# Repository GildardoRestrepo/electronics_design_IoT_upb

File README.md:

# Diseño Electrónico — UPB

Este repositorio reúne todas las actividades del curso **Diseño Electrónico** (UPB). El curso combina una parte **teórica sobre inteligencia artificial** y una parte **práctica sobre IoT, sistemas embebidos y diseño electrónico**: firmware para ESP32, servidores MQTT, dashboards y diseño de PCB en KiCad.

**Autor:** Gildardo Estevan Restrepo Duque

## Actividades

| #  | Actividad                                   | Carpeta                                                | Bitácora                                                                 |
| -- | ------------------------------------------- | ------------------------------------------------------ | ------------------------------------------------------------------------ |
| 01 | Conexión a Ubidots                          | [`01_ubidots_connection`](01_ubidots_connection)       | [01_ubidots_connection.md](_docs/01_ubidots_connection.md)               |
| 02 | Suscripción a Ubidots (downlinks)           | [`02_ubidots_subscription`](02_ubidots_subscription)   | [02_ubidots_subscription.md](_docs/02_ubidots_subscription.md)           |
| 03 | Access Point + servidor web                 | [`03_webserver_accesspoint`](03_webserver_accesspoint) | [03_webserver_accesspoint.md](_docs/03_webserver_accesspoint.md)         |
| 04 | Repositorio de entregables                  | —                                                      | [04_repositorio_entregables.md](_docs/04_repositorio_entregables.md)     |
| 05 | MQTT local: Mosquitto + Node-RED            | [`05_mqtt_local_nodered`](05_mqtt_local_nodered)       | [05_mqtt_local_nodered.md](_docs/05_mqtt_local_nodered.md)               |
| 06 | MQTT en la nube: AWS + Mosquitto + Node-RED | [`06_mqtt_in_aws`](06_mqtt_in_aws)                     | [06_mqtt_in_aws.md](_docs/06_mqtt_in_aws.md)                             |
| 08 | Introducción al flujo de trabajo en KiCad   | [`08_kicad_flow_work`](08_kicad_flow_work)             | [08_kicad_flow_work.md](_docs/08_kicad_flow_work.md)                     |
| 09 | Fuente de poder en KiCad                    | [`09_power_supply`](09_power_supply)                   | [09_power_supply.md](_docs/09_power_supply.md)                           |

Cada bitácora de [`_docs/`](_docs) explica el objetivo, el montaje y cómo reproducir la práctica. Los valores reales de Wi-Fi, tokens y contraseñas no se versionan: cada proyecto trae un archivo de ejemplo (`secrets.h.example`) o marcadores para completar localmente.

La carpeta [`.claude/skills/kicad-flow`](.claude/skills/kicad-flow) contiene el flujo de trabajo para diseñar y verificar los proyectos de KiCad con Claude Code.

## Licencia

MIT. Ver [LICENSE](LICENSE).

---
## Enlaces
[[diseno_electronico_iot|Diseño Electrónico IoT]]

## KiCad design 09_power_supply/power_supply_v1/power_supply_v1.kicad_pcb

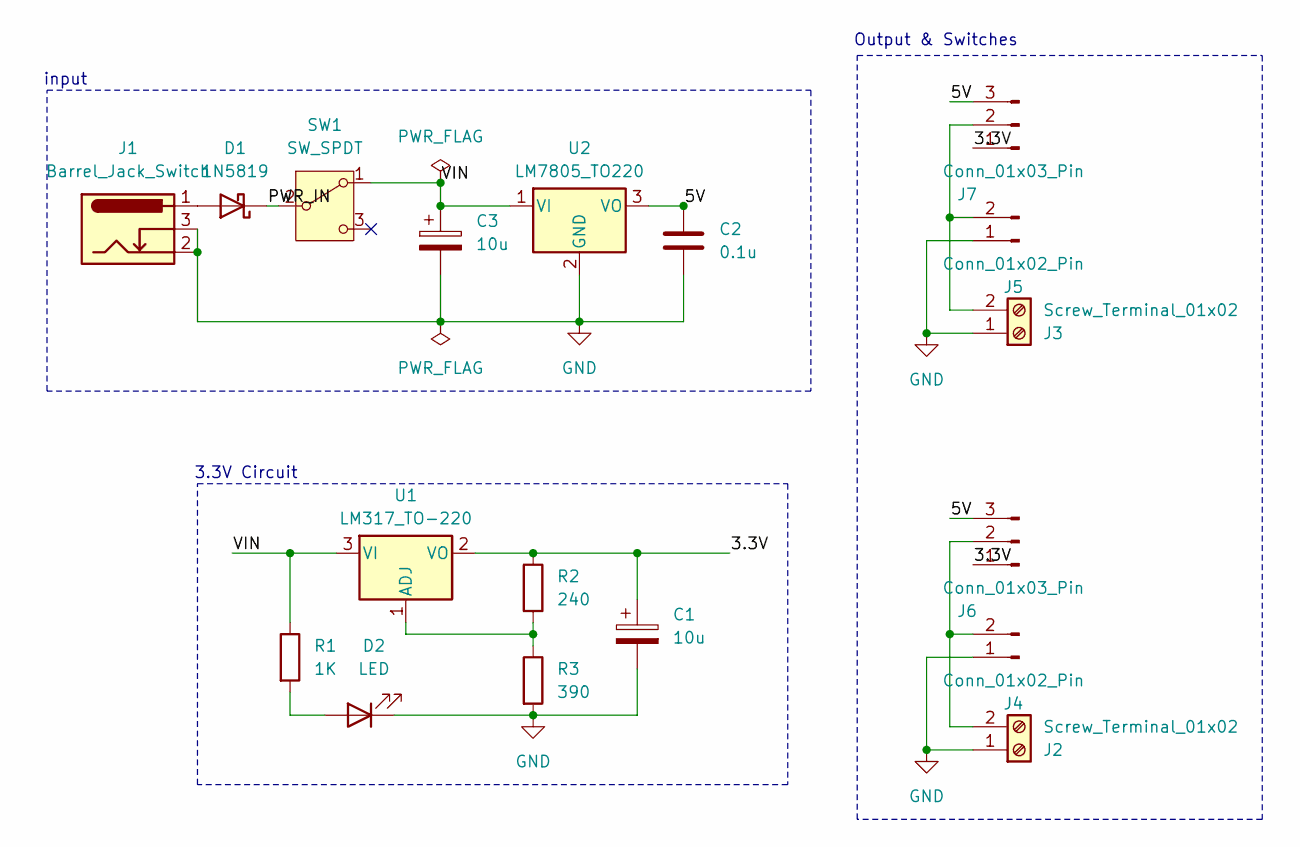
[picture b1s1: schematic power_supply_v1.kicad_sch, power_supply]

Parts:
C1, C3: 10u; CP_Radial_D5.0mm_P2.00mm
C2: 0.1u; C_Disc_D5.0mm_W2.5mm_P5.00mm
D1: 1N5819; D_DO-41_SOD81_P7.62mm_Horizontal
D2: LED; LED_D5.0mm
J1: Barrel_Jack_Switch; BarrelJack_Horizontal
J2, J3: Screw_Terminal_01x02; TerminalBlock_Phoenix_MKDS-1,5-2_1x02_P5.00mm_Horizontal
J4, J5: Conn_01x02_Pin; PinHeader_1x02_P2.54mm_Vertical
J6, J7: Conn_01x03_Pin; PinHeader_1x03_P2.54mm_Vertical
R1: 1K; R_Axial_DIN0207_L6.3mm_D2.5mm_P7.62mm_Horizontal
R2: 240; R_Axial_DIN0207_L6.3mm_D2.5mm_P7.62mm_Horizontal
R3: 390; R_Axial_DIN0207_L6.3mm_D2.5mm_P7.62mm_Horizontal
SW1: SW_SPDT; SW_Slide_SPDT_Straight_CK_OS102011MS2Q
U1: LM317_TO-220; TO-220-3_Horizontal_TabDown
U2: LM7805_TO220; TO-220-3_Horizontal_TabDown

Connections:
/3.3V: C1.1, J6.1, J7.1, R2.1, U1.2 (VO)
/5V: C2.1, J6.3, J7.3, U2.3 (VO)
/PWR_IN: D1.1 (K), SW1.2 (B)
/VIN: C3.1, R1.1, SW1.1 (A), U1.3 (VI), U2.1 (VI)
GND: C1.2, C2.2, C3.2, D2.1 (K), J1.2, J1.3, J2.1, J3.1, J4.1, J5.1, R3.2, U2.2 (GND)
unnamed: D1.2 (A), J1.1
unnamed: D2.2 (A), R1.2
unnamed: J2.2, J4.2, J6.2
unnamed: J3.2, J5.2, J7.2
unnamed: R2.2, R3.1, U1.1 (ADJ)

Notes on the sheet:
3.3V Circuit
Output & Switches
input

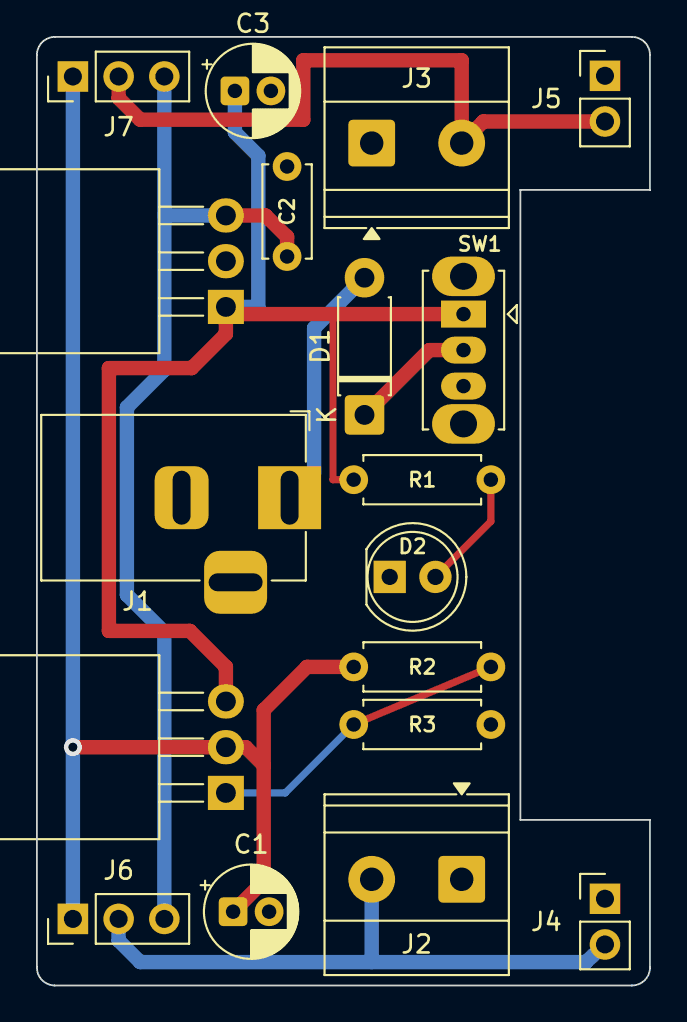
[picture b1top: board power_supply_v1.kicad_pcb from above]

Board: 2 copper layers, 34.1 x 52.7 mm, 18 parts (0 on the bottom side), 10 nets.

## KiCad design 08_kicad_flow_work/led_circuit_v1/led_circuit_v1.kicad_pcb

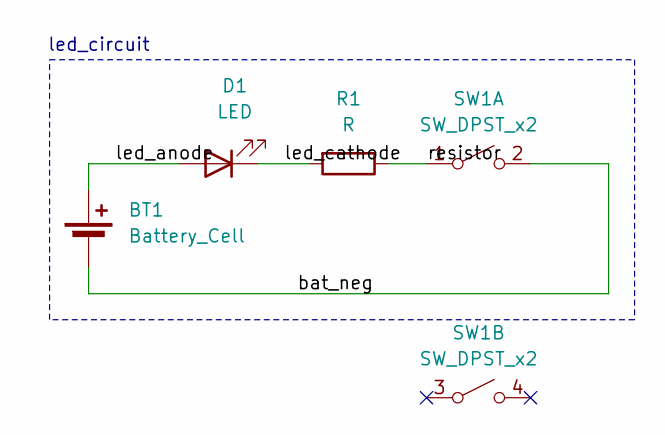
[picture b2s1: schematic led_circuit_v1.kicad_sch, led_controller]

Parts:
BT1: Battery_Cell; BatteryHolder_Keystone_1058_1x2032
D1: LED; LED_D5.0mm
R1: R; R_Axial_DIN0207_L6.3mm_D2.5mm_P10.16mm_Horizontal
SW1: SW_DPST_x2; Push_E-Switch_KS01Q01

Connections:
/bat_neg: BT1.2 (-), SW1.2 (B)
/led_anode: BT1.1 (+), D1.2 (A)
/led_cathode: D1.1 (K), R1.2
/resistor: R1.1, SW1.1 (A)

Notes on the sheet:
led_circuit

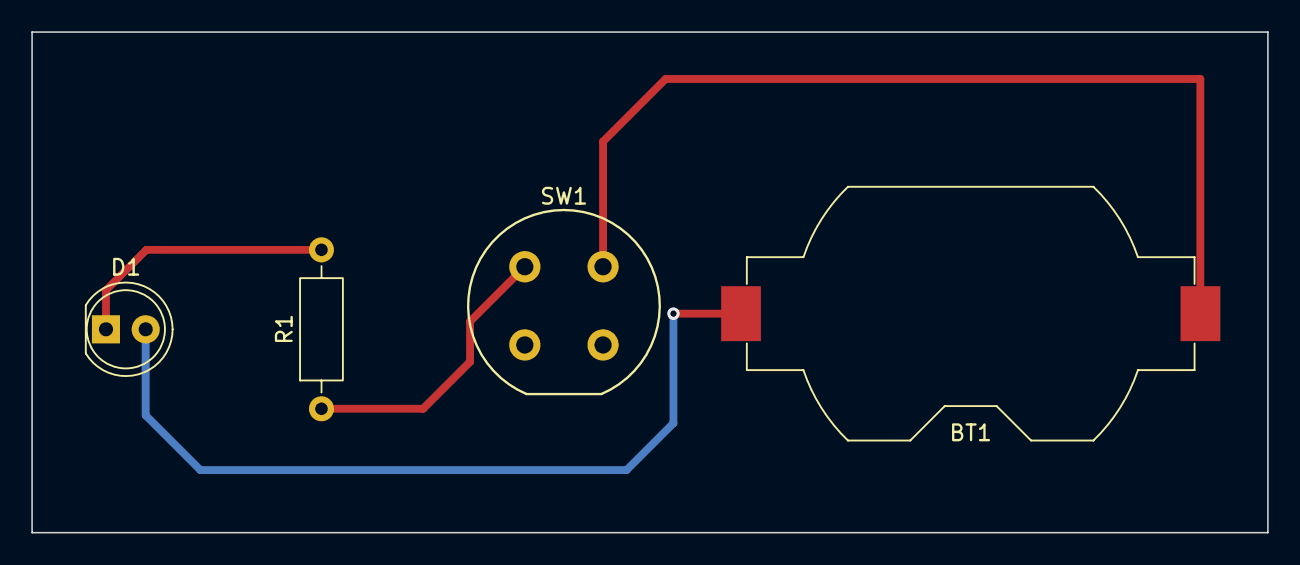
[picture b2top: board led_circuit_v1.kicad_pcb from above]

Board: 2 copper layers, 79.0 x 32.0 mm, 4 parts (0 on the bottom side), 4 nets.
